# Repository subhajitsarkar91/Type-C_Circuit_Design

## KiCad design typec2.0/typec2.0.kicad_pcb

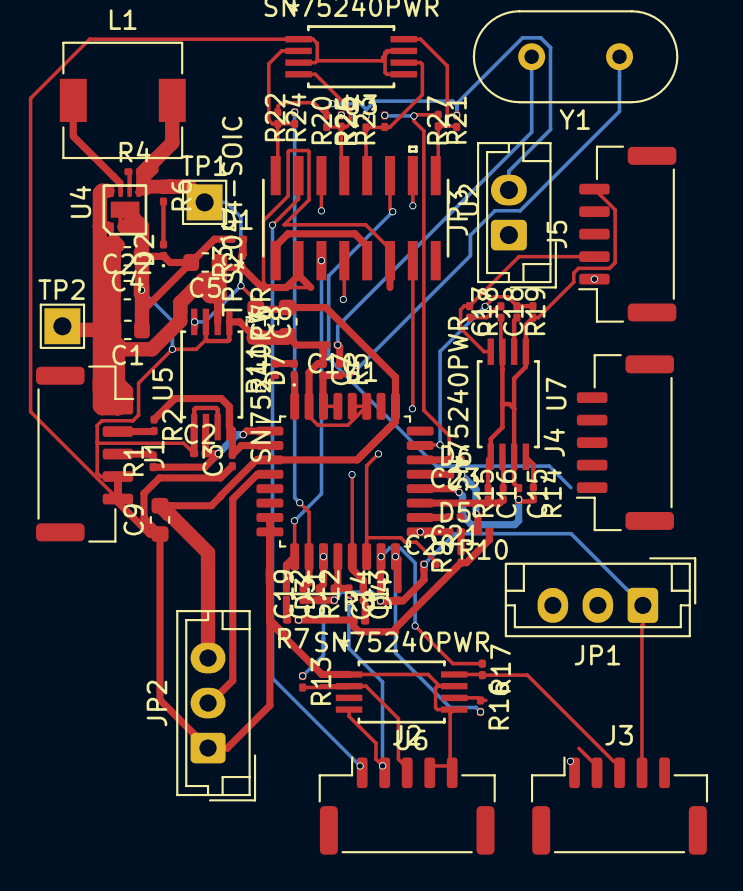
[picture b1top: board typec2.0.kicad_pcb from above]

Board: 4 copper layers, 76 parts (0 on the bottom side), 54 nets.

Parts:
C1, C4, C5, C6: 4.7uf/10V; C_0603_1608Metric
C2, C3, C11, C12, C13, C14, C15, C16, C17, C18: 22pf/10V; C_0201_0603Metric
C7, C10: 33pf/10V; C_0201_0603Metric
C8: 10uf/10V; C_0603_1608Metric
C9: 22uf/10V; C_0603_1608Metric
C19, C20, C21, C23: 0.1uf/10V; C_0201_0603Metric
C22: 4.7 uf/10 V; C_0603_1608Metric
D1, D2, D3, D4, D5, D6, D7: RED; LED_0201_0603Metric
J1: Conn_01x05_Male; JST_GH_SM05B-GHS-TB_1x05-1MP_P1.25mm_Horizontal
J2, J3, J4, J5: Conn_01x05_Female; JST_GH_SM05B-GHS-TB_1x05-1MP_P1.25mm_Horizontal
JP1, JP2: Jumper_3_Open; JST_EH_B3B-EH-A_1x03_P2.50mm_Vertical
JP3: Jumper_NO_Small; JST_EH_B2B-EH-A_1x02_P2.50mm_Vertical
L1: 1uH/2.1A; L_6.3x6.3_H3
R1, R2, R12, R13, R14, R15, R16, R17, R18, R19: 22 E; R_0201_0603Metric
R3, R6, R7, R8, R9, R10, R11: 510 E; R_0201_0603Metric
R4: 178 K; R_0201_0603Metric
R5: 1.5 K; R_0201_0603Metric
R20, R21, R22, R23, R24, R25, R26, R27: 15 K; R_0201_0603Metric
TP1, TP2: TestPoint; TestPoint_THTPad_2.0x2.0mm_Drill1.0mm
U1: TUSB2046
U2: TPS2044-SOIC; TPS2044BDR
U3, U5, U6, U7: SN75240PWR
U4: TPS62082-WSON
Y1: Crystal; Crystal_HC49-U_Vertical

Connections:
GND: C1.1, C2.1, C3.1, C4.1, C5.2, C6.1, C7.1, C8.2, C9.1, C10.2, C11.1, C12.1, C13.1, C14.1, C15.1, C16.1, C17.1, C18.1, C19.1, C20.1, C21.1, C22.2, C23.1, D1.1, D2.1, J1.4, J1.5, J2.4, J2.5, J3.4, J3.5, J4.4, J4.5, J5.4, J5.5, JP1.1, JP2.1, U1.7, U1.8, U1.27, U1.28, U1.31, U2.1, U2.5, U3.1, U3.3, U3.5, U3.7, U4.2, U4.3, U4.4, U4.9, U5.1, U5.3, U5.5, U5.7, U6.1, U6.3, U6.5, U6.7, U7.1, U7.3, U7.5, U7.7
unnamed: C2.2, R1.1, U1.1, U5.6
unnamed: C3.2, R2.1, U1.2, U5.8
unnamed: C7.2, R5.2, U1.29, U1.30, Y1.1
unnamed: C10.1, R5.1, Y1.2
unnamed: C11.2, R12.2, U1.12
unnamed: C12.2, R13.1, U1.11
unnamed: C13.2, R16.2, U1.16
unnamed: C14.2, R17.1, U1.15
unnamed: C15.2, R14.2, U1.20
unnamed: C16.2, R15.1, U1.19
unnamed: C17.2, R18.2, U1.24
unnamed: C18.2, R19.1, U1.23
unnamed: C19.2, R22.2, U1.10
unnamed: C20.2, R20.2, U1.14
unnamed: C21.2, C23.2, R21.1, R23.2, U1.18, U1.22
unnamed: D1.2, R3.2
unnamed: D2.2, R6.2
unnamed: D3.1, U1.9, U2.3
unnamed: D3.2, R7.2
unnamed: D4.1, U1.13, U2.4
unnamed: D4.2, R8.2
unnamed: D5.1, U1.17, U2.7
unnamed: D5.2, R9.2
unnamed: D6.1, U1.21, U2.8
unnamed: D6.2, R10.2
unnamed: D7.2, R11.2
unnamed: J1.2, R2.2
unnamed: J1.3, R1.2
unnamed: J2.2, R12.1, U6.4
unnamed: J2.3, R13.2, U6.2
unnamed: J3.2, R16.1, U6.6
unnamed: J3.3, R17.2, U6.8
unnamed: J4.2, R14.1, U7.4
unnamed: J4.3, R15.2, U7.2
unnamed: J5.2, R18.1, U7.8
unnamed: J5.3, R19.2, U7.6
unnamed: JP1.2, U1.26
unnamed: JP2.2, U1.4
unnamed: JP3.1, R7.1, R8.1, R9.1, R10.1, R11.1
unnamed: L1.1, U4.7
unnamed: R4.1, U4.6
unnamed: R20.1, R25.2, U2.13, U3.4
unnamed: R21.2, R27.1, U2.9, U3.8
unnamed: R22.1, R24.2, U2.16, U3.2
unnamed: R23.1, R26.1, U2.12, U3.6
SUSPND: D7.1, U1.32
VBUS(5V): C1.2, C4.2, C5.1, C22.1, J1.1, R3.1, TP2.1, U2.2, U2.6, U4.1, U4.8, U5.2
VOUT1(5V): J2.1, U2.15
VOUT2(5V): J3.1, U2.14
VOUT3(5V): J4.1, U2.11
VOUT4(5V): J5.1, U2.10
VOUT(3.3V): JP3.2, R24.1, R25.1, R26.2, R27.2
Vout(3.3V): C6.2, C8.1, C9.2, JP1.3, JP2.3, L1.2, R4.2, R6.1, TP1.1, U1.3, U1.25, U4.5, U5.4

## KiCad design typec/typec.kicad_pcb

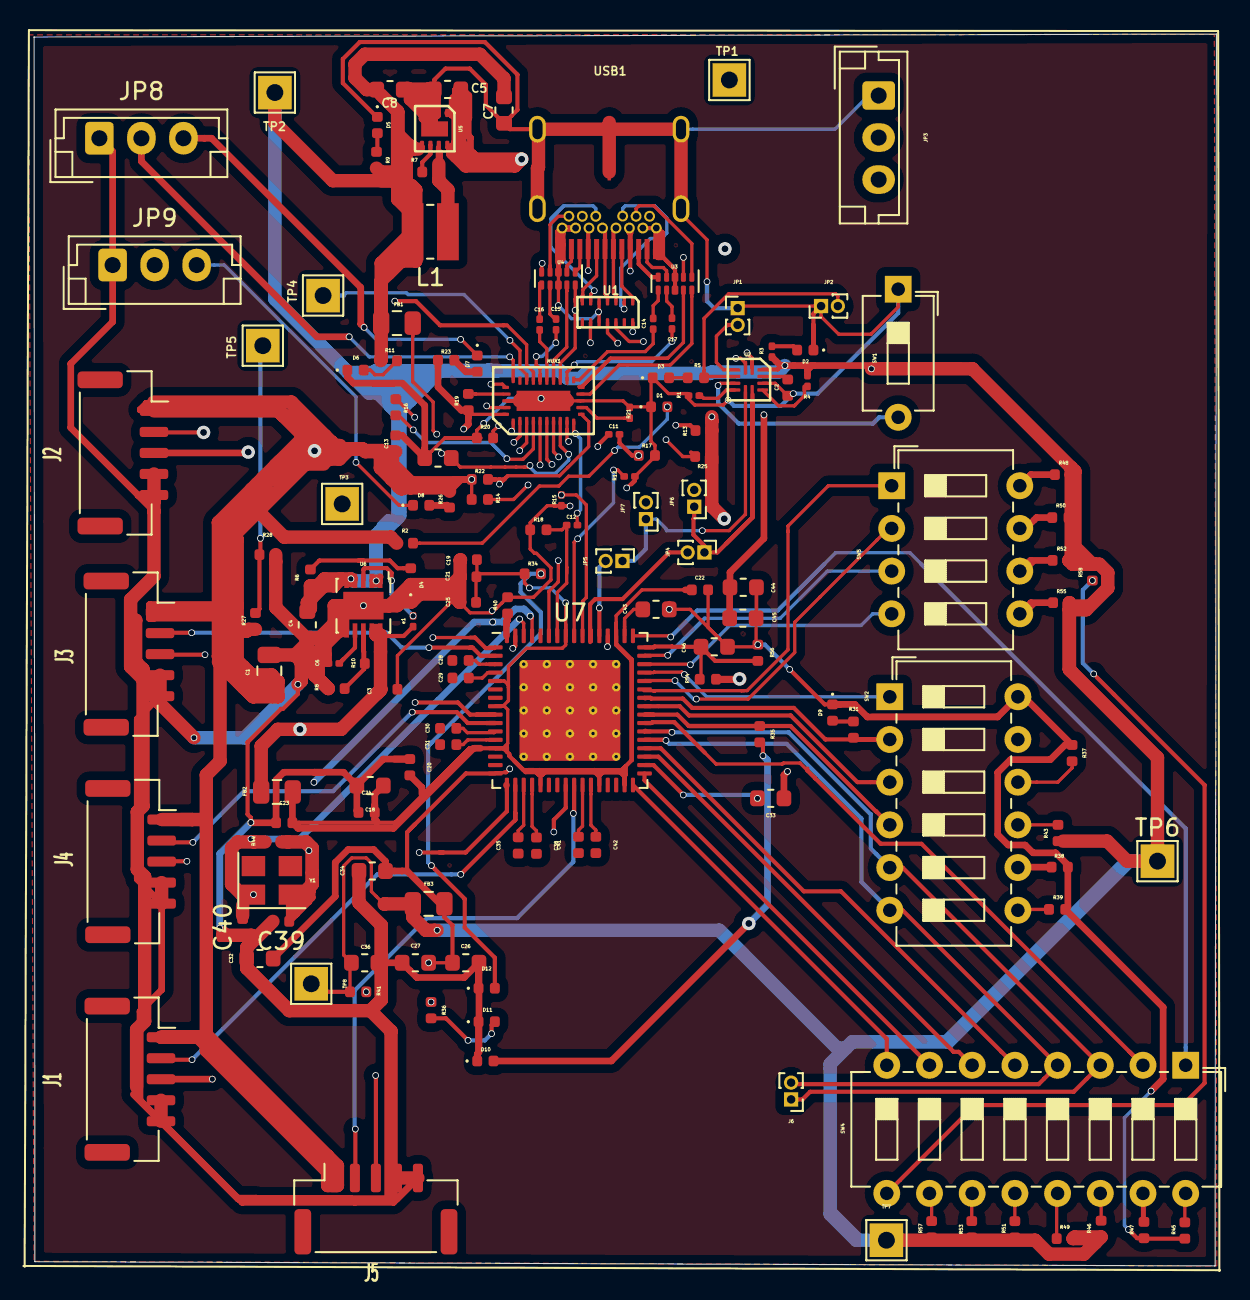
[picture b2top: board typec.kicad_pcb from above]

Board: 4 copper layers, 70.3 x 73.3 mm, 150 parts (0 on the bottom side), 140 nets.

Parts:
C1: 10uf/10v; C_0805_2012Metric
C2, C19, C20, C21, C22, C23, C24, C25, C28, C29, C30, C31, C35, C38, C41, C42: 0.1uF/10v; C_0402_1005Metric
C3: 10uf/10v; C_0402_1005Metric
C4, C36, C44, C45: 1uf/10v; C_0603_1608Metric
C5: 10 uF/10V; C_0603_1608Metric
C6: 590pf/10v; C_0201_0603Metric
C7: 22uf/6.3v; C_0603_1608Metric
C8: 10uf/10v; C_0603_1608Metric
C10: 0.1uf/10v; C_0603_1608Metric
C11, C12, C15: 0.47uf/10v; C_0201_0603Metric
C13: 4.7uf/10v; C_0402_1005Metric
C14, C16, C17: 0.4uf/10v; C_0201_0603Metric
C18, C34: 10uF/10v; C_0603_1608Metric
C26, C27, C32, C33: 0.1uF/10v; C_0603_1608Metric
C39, C40: 18pF/10v; C_0402_1005Metric
C43: 1uF/10v; C_0603_1608Metric
C46: 10 uF/10v; C_0603_1608Metric
D1, D2, D3, D4, D5, D6, D7, D8, D9, D10, D11, D12: LED; LED_0402_1005Metric
FB1, FB2, FB3: Ferrite_Bead; L_0805_2012Metric
J1, J2, J3, J4, J5: Conn_01x05_Female; JST_GH_SM05B-GHS-TB_1x05-1MP_P1.25mm_Horizontal
J6: Conn_01x02_Female; PinHeader_1x02_P1.00mm_Vertical
JP1, JP2: Jumper_NO_Small; PinHeader_1x02_P1.00mm_Vertical
JP3, JP8, JP9: Jumper_3_Open; JST_EH_B3B-EH-A_1x03_P2.50mm_Vertical
JP4, JP5, JP6, JP7: Jumper_2_Open; PinHeader_1x02_P1.00mm_Vertical
L1: 1 uH/3.1A; L_Wuerth_MAPI-3015
MUX1: HD3SS3220; HD3SS3220-VQFN-MUX
R1: 1.6K; R_0201_0603Metric
R2, R6, R9, R11, R31, R34, R35, R36: 330 E; R_0402_1005Metric
R3: 330 E; R_0201_0603Metric
R4: 43K; R_0201_0603Metric
R5: 100 E; R_0402_1005Metric
R7: 178K; R_0402_1005Metric
R8: 5 K; R_0402_1005Metric
R10: 1.9K; R_0402_1005Metric
R12, R15: 100K; R_0201_0603Metric
R13, R48, R50, R52, R55, R56: 10 K; R_0402_1005Metric
R14: 900 K; R_0402_1005Metric
R16: 4.7K; R_0402_1005Metric
R17, R18: 100K; R_0402_1005Metric
R19, R22, R25: 200 K; R_0402_1005Metric
R20: 0 E; R_0402_1005Metric
R21: 0 E; R_0201_0603Metric
R23, R26: 500 E; R_0402_1005Metric
R27: NC / 10 K; R_0402_1005Metric
R28: NC/ 10 K; R_0402_1005Metric
R37, R38, R39, R41, R43, R45, R46, R47, R49: 1 K; R_0402_1005Metric
R40: 9.53 K; R_0402_1005Metric
R44: 1 M; R_0402_1005Metric
R51, R53, R57, R58: 4.7 K; R_0402_1005Metric
R54: 90.9 K; R_0402_1005Metric
SW1: SW_Push_Dual_x2; SW_DIP_SPSTx01_Slide_6.7x4.1mm_W7.62mm_P2.54mm_LowProfile
SW2: SW_DIP_x06; SW_DIP_SPSTx06_Slide_6.7x16.8mm_W7.62mm_P2.54mm_LowProfile
SW4: SW_DIP_x08; SW_DIP_SPSTx08_Slide_6.7x21.88mm_W7.62mm_P2.54mm_LowProfile
SW5: SW_DIP_x04; SW_DIP_SPSTx04_Slide_6.7x11.72mm_W7.62mm_P2.54mm_LowProfile
TP1, TP2, TP3, TP4, TP5, TP6, TP7, TP8: TestPoint; TestPoint_THTPad_2.0x2.0mm_Drill1.0mm
U1: TPD6E05U06-USON
U2: TUSB212-X2QFN
U3, U4: TPD4E05U06-USON
U5: TPS62082-WSON
U6: TPS74801-VSON
U7: USB_HUB; QFN-64-1EP_9x9mm_P0.5mm_EP6x6mm_ThermalVias
USB1: Wurth-632723300011; Wurth-632723300011-MaximumExtensionMount
Y1: 24 MHz; Crystal_SMD_3225-4Pin_3.2x2.5mm
e1: 105 K; R_0201_0603Metric

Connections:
ADDR: MUX1.22, R27.2, R28.1, TP5.1
AUTOENZ: SW2.1, U7.45
CC1: U1.1, USB1.5
CC2: U1.6, USB1.17
CC10: MUX1.2, U1.14
CC20: MUX1.1, U1.9
CRX1N: U3.1, USB1.22
CRX1N0: MUX1.14, U3.10
CRX1P: U3.2, USB1.23
CRX1P0: MUX1.15, U3.9
CRX2N: U4.1, USB1.10
CRX2N0: MUX1.18, U4.10
CRX2P: U4.2, USB1.11
CRX2P0: MUX1.19, U4.9
CSBU1: U1.7, USB1.8
CSBU2: U1.2, USB1.20
CTX1N: U3.5, USB1.3
CTX1N0: C14.1, U3.6
CTX1P: U3.4, USB1.2
CTX1P0: C17.2, U3.7
CTX2N: U4.5, USB1.15
CTX2N0: C16.2, U4.6
CTX2P: U4.4, USB1.14
CTX2P0: C15.2, U4.7
D1+: J3.3, U7.1
D1-: J3.2, U7.2
D2+: J4.3, U7.9
D2-: J4.2, U7.10
D3+: J1.3, U7.17
D3-: J1.2, U7.18
D4+: J5.3, U7.24
D4-: J5.2, U7.25
DIR: MUX1.11, R22.2, TP3.1
FULLPWRMGMTZ_SS_UP: R35.1, SW2.4, U7.40
GANGED_HS_UP: R31.1, SW2.2, U7.42
GND: C1.2, C2.2, C3.2, C4.2, C5.2, C6.2, C7.2, C8.2, C10.2, C13.1, C18.2, C19.1, C20.1, C21.1, C22.1, C23.1, C24.1, C25.1, C26.1, C27.1, C32.1, C33.1, C34.2, C36.2, C39.2, C40.1, C43.2, C44.2, C45.2, C46.1, D1.1, D2.1, D3.1, D4.1, D5.1, D6.1, D9.1, D10.1, D11.1, D12.1, J1.4, J1.5, J2.4, J2.5, J3.4, J3.5, J4.4, J4.5, J5.4, J5.5, JP1.1, JP2.1, JP3.1, JP8.1, JP9.1, MUX1.13, MUX1.28, MUX1.31, R1.2, R8.1, R12.2, R15.1, R17.2, R18.2, R20.1, R21.2, R28.2, R37.1, R38.1, R39.1, R40.2, R45.2, R47.1, R56.1, SW1.1, SW2.12, U1.5, U1.10, U2.10, U3.3, U3.8, U4.3, U4.8, U5.2, U5.3, U5.4, U5.9, U6.6, U6.11, U7.65, USB1.1, USB1.12, USB1.13, USB1.24, USB1.25, USB1.26, USB1.27
INT_NOUT3: MUX1.23, R25.2, TP4.1
unnamed: C2.1, U2.11
unnamed: C6.1, U6.7
unnamed: C10.1, FB1.2, MUX1.8
unnamed: C11.1, MUX1.9
unnamed: C12.1, MUX1.10
unnamed: C14.2, MUX1.16
unnamed: C15.1, MUX1.21
unnamed: C16.1, MUX1.20
unnamed: C17.1, MUX1.17
unnamed: C18.1, C19.2, C20.2, C21.2, C22.2, C23.2, C24.2, C25.2, FB2.2, R34.1, U7.5, U7.8, U7.13, U7.21, U7.28, U7.31, U7.51, U7.57
unnamed: C26.2, C27.2, C32.2, C33.2, C34.1, FB3.2, R36.1, U7.16, U7.34, U7.52, U7.63
unnamed: C28.2, U7.3
unnamed: C29.1, U7.4
unnamed: C30.2, U7.11
unnamed: C31.1, U7.12
unnamed: C35.2, U7.19
unnamed: C38.1, U7.20
unnamed: C39.1, R44.1, U7.61, Y1.2
unnamed: C40.2, R44.2, U7.62, Y1.1
unnamed: C41.2, U7.26
unnamed: C42.1, U7.27
unnamed: C43.1, U7.50
unnamed: C46.2, R54.1, R56.2, U7.48
unnamed: D1.2, R2.2
unnamed: D2.2, R3.2
unnamed: D3.2, R5.2
unnamed: D4.2, R6.2
unnamed: D5.2, R9.2
unnamed: D6.2, R11.2
unnamed: D7.1, JP8.3
unnamed: D7.2, R23.2
unnamed: D8.1, JP9.3
unnamed: D8.2, R26.2
unnamed: D9.2, R31.2
unnamed: D10.2, R35.2
unnamed: D11.2, R36.2
unnamed: D12.2, R34.2
unnamed: J2.2, JP6.2
unnamed: J2.3, JP7.2
unnamed: JP1.2, U2.3
unnamed: JP3.2, R16.1
unnamed: JP4.2, U7.54
unnamed: JP5.2, U7.53
unnamed: L1.1, U5.7
unnamed: MUX1.3, R13.1
unnamed: MUX1.4, R16.2
unnamed: MUX1.5, R14.1
unnamed: MUX1.12, R21.1
unnamed: MUX1.27, R19.1
unnamed: MUX1.29, R20.2
unnamed: R1.1, U2.6
unnamed: R4.2, U2.9
unnamed: R7.1, U5.6
unnamed: R8.2, R10.2, U6.8
unnamed: R37.2, SW2.10
unnamed: R38.2, SW2.8
unnamed: R39.2, SW2.7
unnamed: R40.1, U7.64
unnamed: R41.2, SW2.11
unnamed: R43.2, SW2.9
unnamed: R45.1, SW4.16
unnamed: R46.1, SW4.14
unnamed: R47.2, SW4.15
unnamed: R48.1, SW5.8
unnamed: R49.1, SW4.13
unnamed: R50.1, SW5.7
unnamed: R51.1, SW4.12
unnamed: R52.1, SW5.6
unnamed: R53.1, SW4.11
unnamed: R55.1, SW5.5
unnamed: R57.1, SW4.10
unnamed: R58.1, SW4.9
unnamed: SW1.2, U2.5
unnamed: U6.3, e1.1
OVERCUR1z: SW5.4, U7.46
OVERCUR2z: SW5.3, U7.47
OVERCUR3z: SW5.2, U7.44
OVERCUR4z: SW5.1, U7.43
PWRCTL_POL_TDO: SW2.3, U7.41
PWRON1_BATEN1: SW4.5, U7.36
PWRON2_BATEN2: SW4.6, U7.35
PWRON3_BATEN3: SW4.7, U7.33
PWRON4_BATEN4: SW4.8, U7.32
SCL: JP2.2, R5.1, U2.4
SCLOUT2: JP9.2, MUX1.26
SCL_SMBCLK: J6.1, SW2.5, SW4.3, U7.38
SDAOUT1: JP8.2, MUX1.25
SDA_SMBDAT: J6.2, SW2.6, SW4.4, U7.37
SMBUSZ: SW4.2, U7.39
TEST_TRSTZ: SW4.1, U7.49
USB2_N: U1.3, USB1.6, USB1.19
USB2_N0: U1.12, U2.1
USB2_N10: JP4.1, JP6.1, U2.8
USB2_P: U1.4, USB1.7, USB1.18
USB2_P0: U1.11, U2.2
USB2_P10: JP5.1, JP7.1, U2.7
USB3_RX0N: C11.2, R17.1, U7.59
USB3_RX0P: C12.2, R18.1, U7.58
USB3_TX0N: MUX1.6, R12.1, U7.56
USB3_TX0P: MUX1.7, R15.2, U7.55
VBUS: C1.1, C5.1, C13.2, J1.1, J2.1, J3.1, J4.1, J5.1, JP3.3, MUX1.30, R2.1, R13.2, R14.2, R19.2, R22.1, R23.1, R25.1, R26.1, R27.1, R54.2, TP1.1, U5.1, U5.8, USB1.4, USB1.9, USB1.16, USB1.21
VOUT(1.1V): C3.1, FB2.1, R10.1, U6.9, U6.10, e1.2
VOUT(3.3V): C4.1, C7.1, C8.1, C36.1, C44.1, C45.1, FB1.1, FB3.1, L1.2, R3.1, R4.1, R6.1, R7.2, R9.1, R11.1, R41.1, R43.1, R46.2, R48.2, R49.2, R50.2, R51.2, R52.2, R53.2, R55.2, R57.2, R58.2, TP2.1, TP6.1, TP7.1, TP8.1, U2.12, U5.5, U6.1, U6.2, U6.4, U6.5

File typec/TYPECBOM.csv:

Id,Designator,Package,Quantity,Designation,Supplier and ref,,
1,"J2(POWER&D+D-),J1,J3,J4,J5",JST_GH_SM05B-GHS-TB_1x05-1MP_P1.25mm_Horizontal,5,Conn_01x05_Female,https://www.digikey.in/product-detail/en/jst-sales-america-i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,,
2,"C36,C4,C44,C45",C_0603_1608Metric,4,1uf/10v,https://www.digikey.com/product-detail/en/samsung-electro-me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,,
3,U6,TPS74801-VSON,1,TPS74801-VSON,https://www.digikey.com/product-detail/en/texas-instruments/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,,
4,SW5,SW_DIP_SPSTx04_Slide_6.7x11.72mm_W7.62mm_P2.54mm_LowProfile,1,SW_DIP_x04,https://www.digikey.com/product-detail/en/c-k/BD04/CKN3003-N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,,
5,"TP8,TP3,TP4,TP1,TP2,TP5,TP6,TP7",TestPoint_THTPad_2.0x2.0mm_Drill1.0mm,8,TestPoint,,,
6,U2,TUSB212-X2QFN,1,TUSB212-X2QFN,https://www.digikey.com/product-detail/en/texas-instruments/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,,
7,MUX1,HD3SS3220-VQFN-MUX,1,HD3SS3220,https://www.digikey.com/product-detail/en/texas-instruments/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,,
8,"R23,R26",R_0402_1005Metric,2,500 E,https://www.digikey.com/product-detail/en/vishay-dale/PNM040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,,
9,"U3,U4",TPD4E05U06-USON,2,TPD4E05U06-USON,https://www.digikey.com/product-detail/en/texas-instruments/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,,
10,C13,C_0402_1005Metric,1,4.7uf/10v,https://www.digikey.com/product-detail/en/murata-electronics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,,
11,"R19,R22,R25",R_0402_1005Metric,3,200 K,https://www.digikey.com/product-detail/en/panasonic-electron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,,
12,R16,R_0402_1005Metric,1,4.7K,https://www.digikey.com/product-detail/en/yageo/RC0402JR-074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,,
13,"D7,D8,D6,D1,D4,D2,D3,D5,D9,D11,D12,D10",LED_0402_1005Metric,12,LED,www.digikey.in/product-detail/en/kingbright/APG0603SYC-TT/754-2025-1-ND/6072772,https://www.digikey.in/product-detail/en/kingbright/APG0603V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,https://www.digikey.in/product-detail/en/kingbright/APG0603S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
14,"R13,R48,R50,R52,R55,R56",R_0402_1005Metric,6,10 K,https://www.digikey.com/product-detail/en/susumu/RG1005P-103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,,
15,"R15,R12",R_0201_0603Metric,2,100K,https://www.digikey.com/product-detail/en/yageo/RC0201FR-071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,,
16,R20,R_0402_1005Metric,1,0 E,https://www.digikey.com/product-detail/en/yageo/RC0402FR-070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,,
17,"R18,R17",R_0402_1005Metric,2,100K,https://www.digikey.com/product-detail/en/panasonic-electron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,,
18,"R11,R6,R2,R9,R31,R34,R35,R36",R_0402_1005Metric,8,330 E,https://www.digikey.com/product-detail/en/te-connectivity-pa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,,
19,R21,R_0201_0603Metric,1,0 E,https://www.digikey.com/product-detail/en/yageo/RC0201JR-070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,,
20,"FB1,FB2,FB3",L_0805_2012Metric,3,Ferrite_Bead,www.digikey.in/product-detail/en/murata-electronics-north-america/BLM21PG221SN1D/490-1054-1-ND/574418,,
21,R14,R_0402_1005Metric,1,900 K,https://www.digikey.com/product-detail/en/yageo/RC0402FR-079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,,
22,"C12,C11,C15",C_0201_0603Metric,3,0.47uf/10v,https://www.digikey.com/product-detail/en/taiyo-yuden/LMK063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,,
23,C10,C_0603_1608Metric,1,0.1uf/10v,https://www.digikey.com/product-detail/en/murata-electronics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,,
24,"C2,C19,C21,C22,C23,C25,C28,C29,C30,C31,C35,C38,C41,C42,C20,C24",C_0402_1005Metric,16,0.1uF/10v,https://www.digikey.com/product-detail/en/murata-electronics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,,
25,USB1,Wurth-632723300011-MaximumExtensionMount,1,Wurth-632723300011,https://www.digikey.com/product-detail/en/wurth-electronics-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,,
26,C1,C_0805_2012Metric,1,10uf/10v,https://www.digikey.com/product-detail/en/samsung-electro-me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,,
27,U1,TPD6E05U06-USON,1,TPD6E05U06-USON,https://www.digikey.com/product-detail/en/texas-instruments/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,,
28,R8,R_0402_1005Metric,1,5 K,https://www.digikey.com/product-detail/en/vishay-dale/PNM040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,,
29,R10,R_0402_1005Metric,1,1.9K,https://www.digikey.com/product-detail/en/vishay-dale/TNPW04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,,
30,C6,C_0201_0603Metric,1,590pf/10v,Keep Open(No Coonection) (For Soft Start Usage) ,,
31,C3,C_0402_1005Metric,1,10uf/10v,https://www.digikey.com/product-detail/en/samsung-electro-me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,,
32,R5,R_0402_1005Metric,1,100 E,https://www.digikey.com/product-detail/en/panasonic-electron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,,
33,SW1,SW_DIP_SPSTx01_Slide_6.7x4.1mm_W7.62mm_P2.54mm_LowProfile,1,SW_Push_Dual_x2,https://www.digikey.com/product-detail/en/c-k/BD01/CKN6012-N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,,
34,R1,R_0201_0603Metric,1,1.6K,https://www.digikey.com/product-detail/en/panasonic-electron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,,
35,R3,R_0201_0603Metric,1,330 E,https://www.digikey.com/product-detail/en/yageo/RC0201JR-073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,,
36,R4,R_0201_0603Metric,1,43K,https://www.digikey.com/product-detail/en/panasonic-electron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,,
37,C5,C_0603_1608Metric,1,10 uF/10V,www.digikey.com/product-detail/en/murata-electronics-north-america/GRM188R61A106KE69J/490-14372-1-ND/6606833,,
38,C7,C_0603_1608Metric,1,22uf/6.3v,www.digikey.com/product-detail/en/murata-electronics-north-america/GRM188R60J226MEA0D/490-7611-1-ND/4280544,,
39,C8,C_0603_1608Metric,1,10uf/10v,www.digikey.com/product-detail/en/murata-electronics-north-america/GRM188R61A106KE69J/490-14372-1-ND/6606833,,
40,L1,L_3x3_H3,1,1 uH/2.2A,www.digikey.in/product-detail/en/wurth-electronics-inc/74404032010/732-5491-1-ND/4865385,,
41,R7,R_0402_1005Metric,1,178K,https://www.digikey.com/product-detail/en/stackpole-electron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,,
42,R27,R_0402_1005Metric,1,NC / 10 K,https://www.digikey.com/product-detail/en/susumu/RG1005P-103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,,
43,R28,R_0402_1005Metric,1,NC/ 10 K,https://www.digikey.com/product-detail/en/susumu/RG1005P-103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,,
44,"C14,C16,C17",C_0201_0603Metric,3,0.4uf/10v,https://www.digikey.com/product-detail/en/taiyo-yuden/LMK063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,,
45,"C26,C27,C32,C33",C_0603_1608Metric,4,0.1uF/10v,www.digikey.com/product-detail/en/kemet/C0603C104K8RACTU/399-1095-1-ND/411370,,
46,"C34,C18",C_0603_1608Metric,2,10uF/10v,www.digikey.com/product-detail/en/murata-electronics-north-america/GRM188R61A106KE69J/490-14372-1-ND/6606833,,
47,"C39,C40",C_0402_1005Metric,2,18pF/10v,www.digikey.com/products/en?keywords=445-13469-1-ND,,
48,C43,C_0603_1608Metric,1,1uF/10v,www.digikey.com/product-detail/en/samsung-electro-mechanics/CL10A105KP8NNNC/1276-1182-1-ND/3889268,,
49,C46,C_0603_1608Metric,1,10 uF/10v,www.digikey.com/product-detail/en/murata-electronics-north-america/GRM188R61A106KE69J/490-14372-1-ND/6606833,,
50,"R37,R38,R39,R41,R43,R45,R46,R47,R49",R_0402_1005Metric,9,1 K,https://www.digikey.com/product-detail/en/panasonic-electron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,,
51,R40,R_0402_1005Metric,1,9.53 K,https://www.digikey.com/product-detail/en/yageo/RC0402FR-079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,,
52,R44,R_0402_1005Metric,1,1 M,https://www.digikey.com/product-detail/en/yageo/RC0402JR-071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,,
53,"R51,R53,R57,R58",R_0402_1005Metric,4,4.7 K,https://www.digikey.com/product-detail/en/yageo/RC0402JR-074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,,
54,R54,R_0402_1005Metric,1,90.9 K,https://www.digikey.com/product-detail/en/stackpole-electron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,,
55,SW2,SW_DIP_SPSTx06_Slide_6.7x16.8mm_W7.62mm_P2.54mm_LowProfile,1,SW_DIP_x06,https://www.digikey.com/product-detail/en/c-k/BD06/CKN3005-N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,,
56,SW4,SW_DIP_SPSTx08_Slide_6.7x21.88mm_W7.62mm_P2.54mm_LowProfile,1,SW_DIP_x08,https://www.digikey.com/product-detail/en/c-k/BD08/CKN3007-N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,,
57,U7,QFN-64-1EP_9x9mm_P0.5mm_EP6x6mm_ThermalVias,1,USB_HUB,www.digikey.in/product-detail/en/texas-instruments/TUSB8042RGCT/296-47475-1-ND/7896964,,
58,Y1,Crystal_SMD_3225-4Pin_3.2x2.5mm,1,24 MHz,www.digikey.com/product-detail/en/kyocera-international-inc-electronic-components/CX3225GB24000P0HPQCC/1253-1198-1-ND/4454036,,
59,U5,TPS62082-WSON,1,TPS62082-WSON,www.digikey.in/product-detail/en/texas-instruments/TPS62082DSGT/296-29647-1-ND/2756421,,
60,e1,R_0201_0603Metric,1,105 K,https://www.digikey.com/product-detail/en/yageo/RC0201FR-071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,,
61,J6,PinHeader_1x02_P1.00mm_Vertical,1,Conn_01x02_Female,www.digikey.in/product-detail/en/sullins-connector-solutions/SMH100-LPSE-S40-ST-BK/S9219-ND/2039523,,
62,"JP3,JP8,JP9",JST_EH_B3B-EH-A_1x03_P2.50mm_Vertical,3,Jumper_3_Open,www.digikey.in/product-detail/en/wurth-electronics-inc/61300311121/732-5316-ND/4846825,,
63,"JP6,JP4,JP5,JP7",PinHeader_1x02_P1.00mm_Vertical,4,Jumper_2_Open,www.digikey.in/product-detail/en/sullins-connector-solutions/SMH100-LPSE-S40-ST-BK/S9219-ND/2039523,,
64,"JP1,JP2",PinHeader_1x02_P1.00mm_Vertical,2,Jumper_NO_Small,www.digikey.in/product-detail/en/sullins-connector-solutions/SMH100-LPSE-S40-ST-BK/S9219-ND/2039523,,

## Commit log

2019-04-22 Second Change
2019-04-24 Added TUSB212 and USB 3.1 Connector
2019-04-24 Added new Circuit diagram
2019-04-24 Added a new sheet
2019-04-25 Added another page and completed the Multiplexer schematics.
2019-04-25 Completed Multiplexer
2019-04-25 Last minute changes
2019-04-26 USB HUB IC ADDED
2019-05-27 Added updated gerber

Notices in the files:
parts and their libraries:
Copyright 2016 Accelerated Designs. All rights reserved.
